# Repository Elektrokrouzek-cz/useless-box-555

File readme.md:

# NE555 based useless box
This is the construction of useless box based on NE555 timers. All components are
in THT packages.

PCB is 2-layer and was designed using KiCad 8. Fabrication output for JLCPCB is in gerber folder.

Happy soldering!

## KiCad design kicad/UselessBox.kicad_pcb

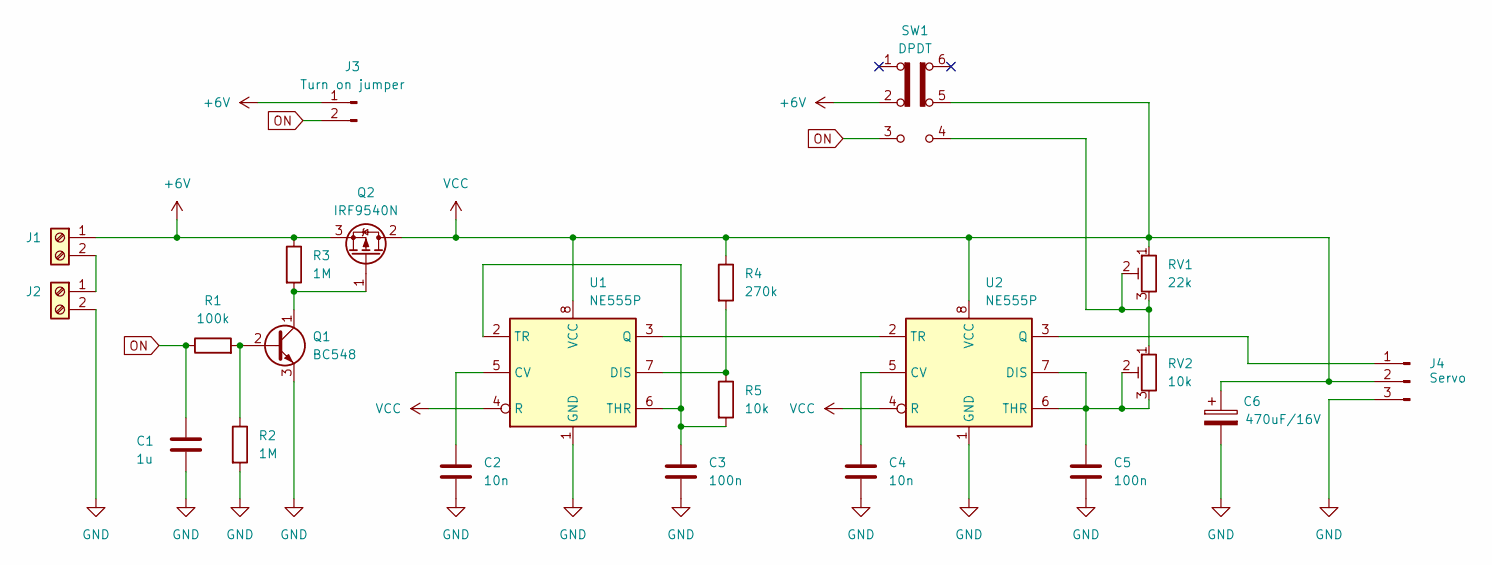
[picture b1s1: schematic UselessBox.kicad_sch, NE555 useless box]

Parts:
C1: 1u; C_Disc_D4.3mm_W1.9mm_P5.00mm
C2, C4: 10n; C_Disc_D4.3mm_W1.9mm_P5.00mm
C3, C5: 100n; C_Disc_D4.3mm_W1.9mm_P5.00mm
C6: 470uF/16V; CP_Radial_D8.0mm_P3.50mm
J1, J2: Screw_Terminal_01x02; TerminalBlock_RND_205-00001_1x02_P5.00mm_Horizontal
J3: Turn on jumper; PinHeader_1x02_P2.54mm_Vertical
J4: Servo; PinHeader_1x03_P2.54mm_Vertical
Q1: BC548; TO-92_Inline
Q2: IRF9540N; TO-220-3_Vertical
R1: 100k; R_Axial_DIN0207_L6.3mm_D2.5mm_P7.62mm_Horizontal
R2, R3: 1M; R_Axial_DIN0207_L6.3mm_D2.5mm_P7.62mm_Horizontal
R4: 270k; R_Axial_DIN0207_L6.3mm_D2.5mm_P7.62mm_Horizontal
R5: 10k; R_Axial_DIN0207_L6.3mm_D2.5mm_P7.62mm_Horizontal
RV1: 22k; Potentiometer_Runtron_RM-065_Vertical
RV2: 10k; Potentiometer_Runtron_RM-065_Vertical
SW1: DPDT; SW_CK_JS202011CQN_DPDT_Straight
U1, U2: NE555P; DIP-8_W7.62mm

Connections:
+6V: J1.1, J3.1, Q2.3 (S), R3.1, SW1.2 (B)
GND: C1.1, C2.2, C3.2, C4.2, C5.2, C6.2, J2.2, J4.3, Q1.3 (E), R2.2, U1.1 (GND), U2.1 (GND)
unnamed: J1.2, J2.1
unnamed: J4.1, U2.3 (Q)
unnamed: Q1.2 (B), R1.2, R2.1
unnamed: Q1.1 (C), Q2.1 (G), R3.2
unnamed: RV1.2, RV1.3, RV2.1, SW1.4 (A)
unnamed: C2.1, U1.5 (CV)
unnamed: R4.2, R5.1, U1.7 (DIS)
unnamed: U1.3 (Q), U2.2 (TR)
unnamed: C3.1, R5.2, U1.2 (TR), U1.6 (THR)
unnamed: C4.1, U2.5 (CV)
unnamed: C5.1, RV2.2, RV2.3, U2.6 (THR), U2.7 (DIS)
ON: C1.2, J3.2, R1.1, SW1.3 (C)
VCC: C6.1, J4.2, Q2.2 (D), R4.1, RV1.1, SW1.5 (B), U1.4 (R), U1.8 (VCC), U2.4 (R), U2.8 (VCC)

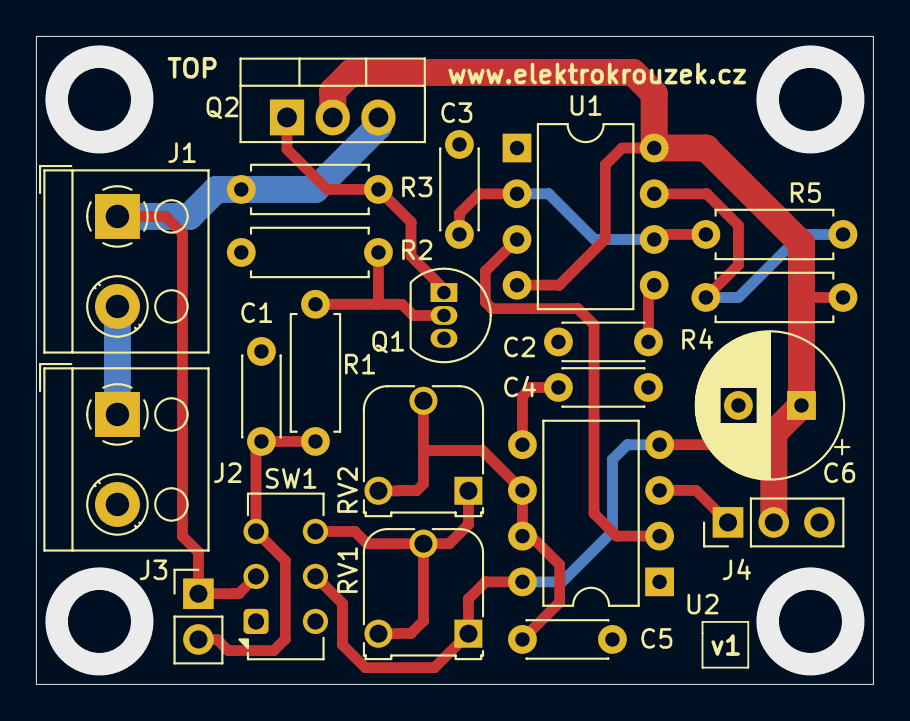
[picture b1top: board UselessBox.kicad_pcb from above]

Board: 2 copper layers, 46.5 x 36.0 mm, 22 parts (0 on the bottom side), 15 nets.

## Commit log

2024-12-30 Schematic added
2024-12-30 Mounting holes mask added
2024-12-30 Turn-on jumper added
2025-02-08 3D models, manuals
2025-03-14 3D model update
